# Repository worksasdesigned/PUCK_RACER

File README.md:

# Puck Racer 🏃‍♂️💨
**The DIY agility System**

## 📖 The Story: Why this exists
Let's be real for a second: I built this because I was simply too stingy to drop **300-400€** on a commercial reaction light system that consists of only 4 pucks, needs a paid subscription and provides 200 extremely similar games... which can be summerized in 5 different game modes.  
**Puck Racer has now 26 games**. Highly adjustable. Multi-Player, Multi-Group support.  
All options combined easily provide 200+ "games" ;-)  

I also noticed that the PE equipment at my kids' elementary school hasn't really changed in 40 years. It was time for an upgrade.

**Puck Racer** is the answer. It’s perfect for professional training support in sports clubs, spicing up PE lessons in schools, or just being the absolute highlight of the next kids' birthday party.  
I would descibe it as a **blaze**ing**POD** - DIY solution - just on steroids :-)  

**The Trade-off:**
Yes, building 4-10 Pucks and a Coordinator is a bit of a grind. It takes time and patience.

**The Reward:**
You get a fully customizable system where the hardware cost per Puck can be pushed **under 20€**. You do the math. 😉  
Nice side effect: Teach your kids how to solder. Its easy to medium difficulty. My 9 year old twins built 5 pucks by them selfe with very little help.  

---

## 🛠 Hardware
*detailed howto and hardware list will be provided once its worth it*  
ESP32-C3 for pucks   (use the one with external antenna or built a small antenna!)
ESP32-S3 for Coordinator  
WS2812B 35LED ring  
something for 18650 Battery placement + stepup to 5V  
Arcade Button (bigger is better) 60mm  
3D printer for pucks  
Soldering Stuff  
**P A T I E N C E** - printing 10 pucks, soldering 10 times the same stuff and initial flashing needs a good amount of patience.

---

## 💻 Software & Installation

This system relies on a **Coordinator** (ESP32-S3) that acts as the brain and the WiFi Access Point, and multiple **Pucks** (ESP32-C3) that communicate via ESP-NOW.

### 📦 Prerequisites

To compile and flash this project, you need the **Arduino IDE**. Of cause VS Code will also work. 

1.  **ESP32 Board Manager:**
    * Go to *Tools > Board > Boards Manager*.
    * Install **esp32 by Espressif Systems**.
    * **Recommended Version:** `3.0.0` or higher (we need proper S3/C3 support).

2.  **Required Libraries:**
    Install these via the Arduino Library Manager:
    * `FastLED` (for the WS2812B LEDs)
    * `ESPAsyncWebServer from ESPhome project` (for the Coordinator Dashboard)
    * `AsyncTCP from ESPhome project` (dependency for the WebServer)

### 📂 Uploading the Web Interface (IMPORTANT!)

The Coordinator runs a modern Web App stored in the ESP32's internal file system (LittleFS). You **must** upload the files from the `data` folder, otherwise, you'll just see a blank screen.

1.  Download the **Arduino LittleFS Upload Tool**:
    * 👉 [GitHub Link: arduino-littlefs-upload](https://github.com/earlephilhower/arduino-littlefs-upload)
2.  Follow the installation instructions on the repo (copy to `tools` folder).
3.  In Arduino IDE, select the Coordinator board.
4.  Click **Tools > ESP32 LittleFS Data Upload**.

### 📡 Connectivity & OTA Updates

**The Network:**
The Coordinator opens a WiFi Access Point (Default SSID: `PuckRace_Trainer`). Connect your phone or laptop to this network and navigate to `http://192.168.42.1`. No app required, it runs in the browser.  It has no pwassword initially. Your choice to set it up if you deal with kids and their smartphones.

**Wireless Updates (OTA):**
You only need to hook the Pucks up to USB *once* for the initial flash. After that, you're free:
1.  Compile the new Puck firmware (Sketch -> Export Compiled Binary).
2.  Go to the Coordinator Web Interface Settings.
3.  Upload the `.bin` file.
4.  Hit **"Update All Pucks"**. The Coordinator will distribute the update wirelessly to all active Pucks. Magic. ✨

After the real first beta is released il will provide the bin files in case of updates. 

---

## 🎮 The Games

**26 games** across 4 categories. Highly adjustable, multi-player and multi-group support.

| Focus | Icon |
|---|---|
| Hand-eye coordination, fast stimulus processing | ⚡ Reaction |
| Rapid direction changes, sprints, footwork | 🏃‍♂️ Agility |
| Cardiovascular load and pacing | 🫀 Endurance |
| Memory, timing, stress resistance | 🧠 Cognition |
| Teambuilding and motivation | 🤪 Fun |
| Practical tools for coaches and teachers | 🛠️ Utility |

---

### ⚡🏃‍♂️ Agility & Reaction

| Game | Players | Pucks | Focus | Highlights |
|------|---------|-------|-------|------------|
| 🎯 **Hunt! (Color Hunt)** | 1–10 | 3–20 | ⚡ 🏃‍♂️ 🧠 | Dynamic queues, adjustable timeout, 1-sec warning |
| ⚡ **React 2-Player** | 2–10 (pairs) | 3–10/group | ⚡ 🧠 | Configurable colors, fake stimuli for confusion |
| 🎯 **Target Touch** | 1–5 groups | 2–10/group | ⚡ 🛠️ | Sequence or random mode, rest time control |
| 🏃‍♂️ **Agility T-Test** | 1–2 groups | 4/group | 🏃‍♂️ | Standard T-test layout, mandatory touch mode |
| 🐱 **Cat Reflex** | 1–11 | 1/player + 1 center | ⚡ | Highlander mode, Color Chaos (false-start training) |
| ⚡🎯 **Catch the light Pro** | 1 | 3–20 | ⚡ 🧠 | Adaptive speed, fake colors, per-puck reaction analysis |

---

### 🫀 Endurance & Pacing

| Game | Players | Pucks | Focus | Highlights |
|------|---------|-------|-------|------------|
| ⏱️ **The Pacemaker** | Groups | 4–20 | 🫀 🧠 | Exact pace (min/km), circle or shuttle, live distance |
| 🏃‍♂️ **Luc Léger (Beep Test)** | 1–10 | 2/player | 🫀 | Official VO₂max tables, false start detection |
| 🏃‍♂️ **Shuttle Run** | 1–5 | 2/player | 🏃‍♂️ 🫀 | Winner detection, false start detection |
| 🧟 **Zombie Escape** | 1–10 groups | 2/group | 🫀 🧠 🤪 | Auto time reduction, sudden death mode |
| 🏎️ **Pit Stop** | 1–10 groups | 1-2/group | 🫀 | Making a break. Defined PitStops. Pitlane mode. |

---

### 🧠🤪 Cognition & Fun

| Game | Players | Pucks | Focus | Highlights |
|------|---------|-------|-------|------------|
| 🔴 **Simon Says** | 1–3 groups | 2–10/group | 🧠 | Adjustable speed, color-blind palette |
| 🏃‍♂️ **Simon Runs** | 1–3 groups | 1 display + inputs | 🧠 🏃‍♂️ | Central display mode, disqualification management |
| 💣 **Bomb Squad** | 1–10 | 1/player | 🧠 🤪 | Adjustable tolerance, group sync mode, explosion feedback |
| 🚦 **Red Light, Green Light** | 1–10 groups | 1–20 | 🤪 ⚡ | Grace period, coach override |
| 🎩 **The Sorting Hat** | 2–100 | 1–3 | 🛠️ 🤪 | Balanced assignment, live rebalance |
| 🧠 **Memory Sprint** | 1+ | 4–20 (pairs) | 🧠 🏃‍♂️ | Blind search mode, auto-restart, live error tracking |
| ⚔️ **Domination (Turf War)** | 2 teams/arena | 2+/arena | 🏃‍♂️ 🫀 | 1-click vs 2-click capture, dual-arena support |
| ❌⭕ **Tactical TicTacToe** | 1–3 groups | 4 / 6 / 7 / 10 | 🧠 | Hard-Mode, grid auto-adapts to puck count |
| 🪑 **Musical Chairs** | 2–13 | Player count −1 | 🤪 🏃‍♂️ | Custom MP3 upload, dynamic round elimination |

---

### 🛠️ Measurement Tools & Utilities

| Game | Players | Focus | Highlights |
|------|---------|-------|------------|
| ⏱️ **Stopwatch** | 1–10 | 🛠️ | Split/lap times, central or individual start, Hold-to-Start |
| ⏳ **Simple Timer** | 1–10 | 🛠️ | Visual countdown fill, live +/− time adjustment per player |
| 🔢 **Simple Counter** | 1–10 | 🛠️ | Tap-to-count, time limit, debounce filter |
| ⬇️ **Simple Countdown** | 1–10 | 🛠️ | Count down from N, stop-on-winner option |
| 🥵 **TABATA Controller** | Unlimited | 🛠️ 🫀 | Synced progress bars, work/rest phases, configurable sound |
| ▶️ **Display Mode** | — | 🛠️ | Manual/sync/random light control for events |

---

### 👥 Player & Training Manager

| Tool | Description |
|------|-------------|
| 👥 **Player Manager** | Manage teams and class lists. Upload/backup CSV. Create named groups for quick name assignment. |
| 📋 **Training Manager** | Define training sequences with up to 3 games and pre-set all parameters. Jump between games without touching the setup screens. |

---

## Technical Updates:  

**V2.88.2**  
    - iOS meta Tags added  
    - App Icon added  
    - Check that only 1 device is connected via WiFi  

**V2.89.7**   
    - Simple Statistics added for players maintained in Playermanager  
    - CatReflexes (avarage reaction time)  
    - BombSquad (avarage reaction time)  
    - Shuttle run (time) assuming trainer always uses same distance, else its just a tracking of usage  
    - Countdown (time and clicks) tracking of usage - Fix of copy&paste error in game_simplecounter_setup.html      
**V2.89.13**  
    - statistics for all relevant games finished  
        - Whac-A-Mole  
        - Pacemaker  
        - React2Player  
        - T-Test  
        - Beep Test  
        - Catch the light (incl. System record)  
    - Player manager with extended Export and Import incl. highscores and statistics   
    - Minor bugfixes in some games (Player-List added, minor layout changes)  
        - fix for Whac-A-Mole color picker  
**V2.89.15**   
    - Tutorial adjusted  

**V2.90.12**   
    - RSSI fixed  
    - 12 games small fixes (puck colo) fixed  
    - snall enhancements in various games after Beta Test 1  

**V2.91.1**   
    - new game: Pit Stop  
    - Red Light Green Light small adjustments and fixes  

**V2.92.3**   
    - rename a game to catch the light  
    - Cat Reflex Highlander Mode adjusted  

**V2.93.0**   
    - Bidirectional heartbeat puck firmware 81  

**V2.94.2**   
    - UI 2.0 new design    

**V2.96.1**   
    - Battery Management and auto Power Saving Mode   
    - Toast Message "low Battery level", "shutdown Puck due to critical battery level"   
    - Puck shutdown (deepsleep) at low Battery level (safety)   
    - Puck blocks reboot under 3,6V Battery level (safety)  
    - Max LED Power Consumption reduced to 1.2A (should only effect white @35LEDs) (safety)   
    - Hardware Watchdog implemented (Puck restarts after 3s off non-reactivity)   

**V2.97.1**   
    - Anti-cache links added (Core version behind urls)   
    - _setup.html remembers settings, when navigation back from _run to _names  to _setup.html    

**V2.98.0**   
    - Gerber and PCB files addes   
    - temperature control, warning and local alarm added   

**V2.99.1**   
    - Test version keygen working in react2p
    - Test version of JSON GAME   

**V3.0.1**   
    - change to OpenSource, Removed c Blocker of Licence key. HTML blocker stays for registration use  
    - Stabilization fix. passed 3h permanent test!   
    - many small fixes.  

--- 

## 🤝 Contributing
Found a bug? Have a game idea? Feel free to open an issue or submit a pull request. Let's make school sports digital (and affordable)!  
**Licence:** Use it, change it, DO NOT SELL it.  see License.txt

*Project by WorksAsDesigned*

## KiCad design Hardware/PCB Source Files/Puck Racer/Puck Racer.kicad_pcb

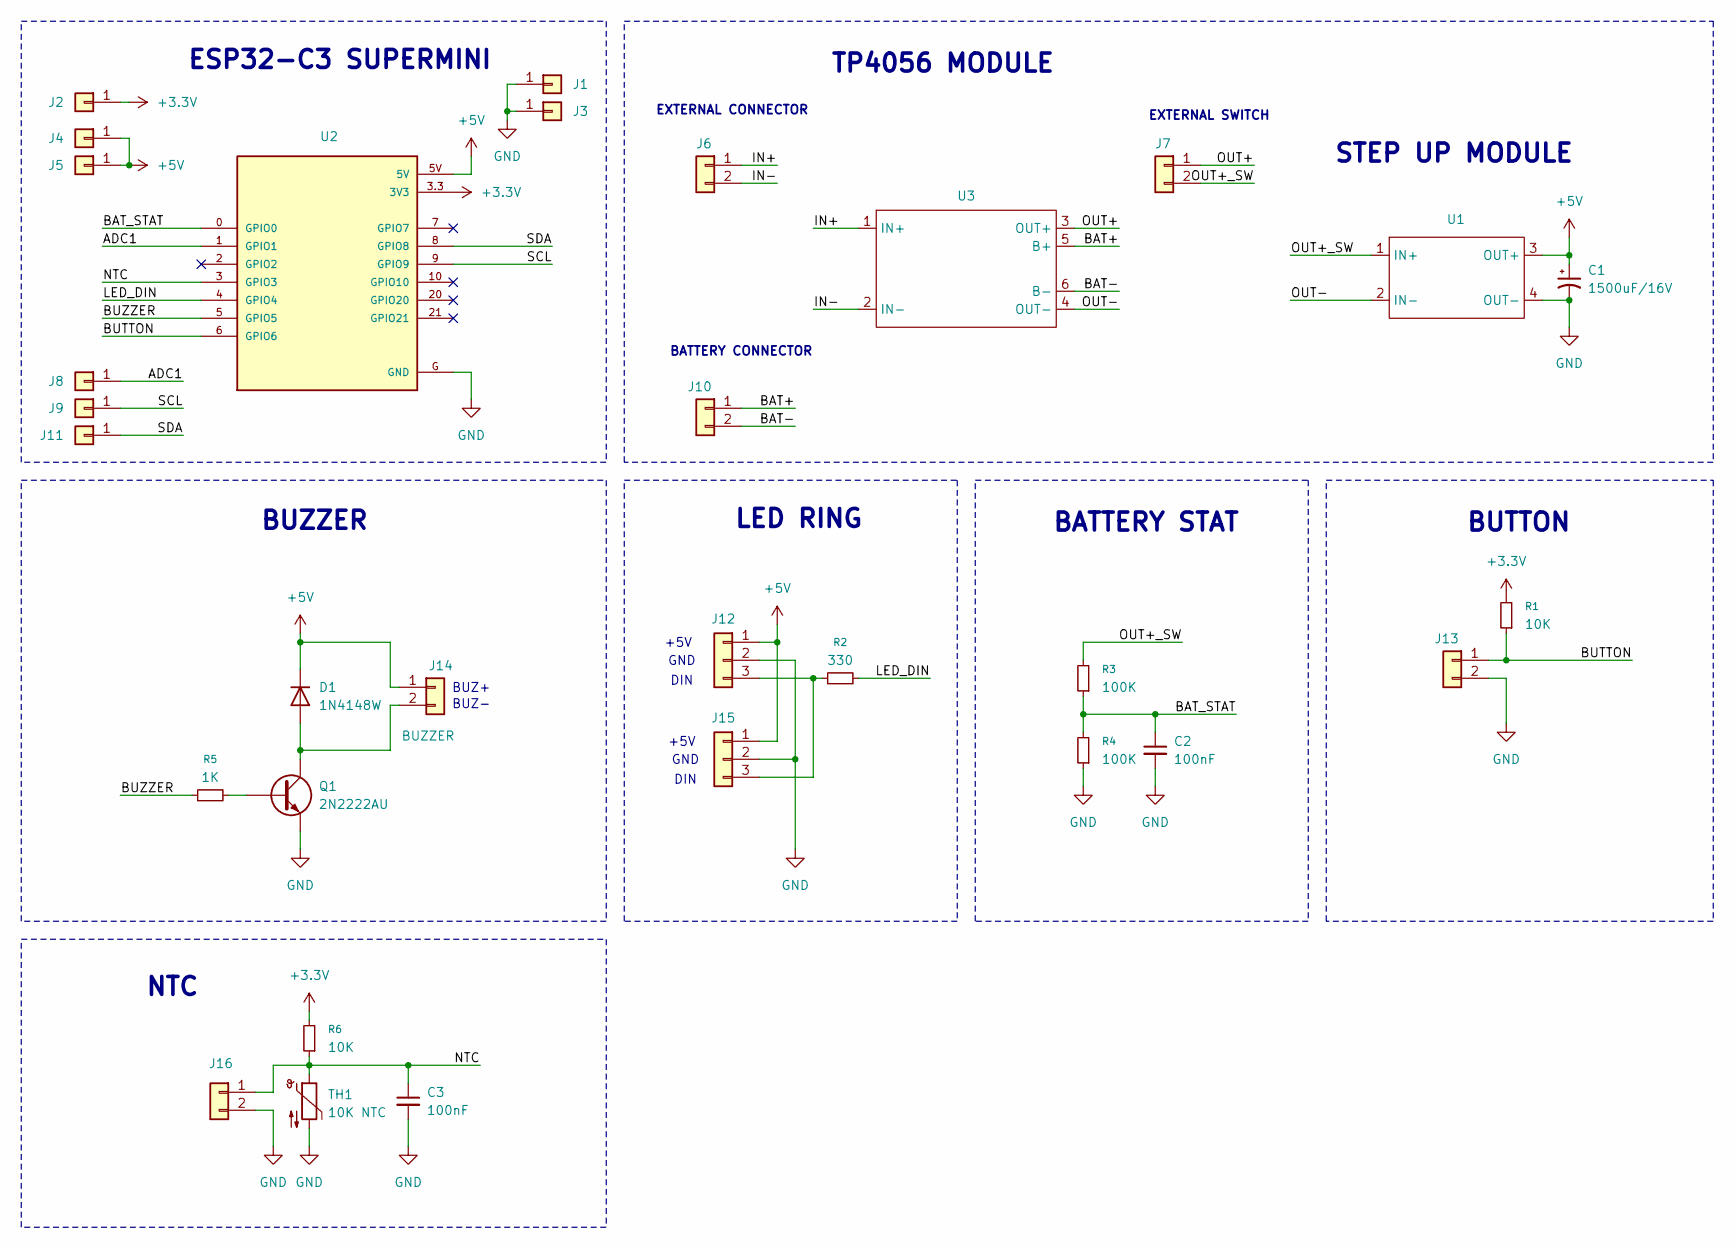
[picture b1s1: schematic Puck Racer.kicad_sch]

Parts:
C1: 1500uF/16V; CP_Radial_D10.0mm_P5.00mm
C2, C3: 100nF; C_0805_2012Metric; JLCPCB Part # C28233
D1: 1N4148W; D_SOD-123; JLCPCB Part # C2099
J1, J2, J3, J4, J5, J8, J9, J11: Conn_01x01; PinHeader_1x01_P2.54mm_Vertical
J6, J7, J10: B2B-XH-A(LF)(SN); JST_XH_B2B-XH-A_1x02_P2.50mm_Vertical; JLCPCB Part # C158012
J12: B3B-XH-A(LF)(SN); JST_XH_B3B-XH-A_1x03_P2.50mm_Vertical; JLCPCB Part # C144394
J13, J16: BUTTON1; PinHeader_1x02_P2.54mm_Vertical
J14: BUZZER; PinHeader_1x02_P2.54mm_Vertical
J15: LED; PinHeader_1x03_P2.54mm_Vertical
Q1: 2N2222AU; SOT-89-3; JLCPCB Part # C21714170
R1, R6: 10K; R_0805_2012Metric; JLCPCB Part # C17414
R2: 330; R_0805_2012Metric; JLCPCB Part # C17630
R3, R4: 100K; R_0805_2012Metric; JLCPCB Part # C25611
R5: 1K; R_0805_2012Metric; JLCPCB Part # C17513
TH1: 10K NTC; R_0805_2012Metric; JLCPCB Part # C95968
U1: Step Up Power Module
U2: ESP32-C3_SUPERMINI_TH; MODULE_ESP32-C3_SUPERMINI_TH
U3: TP4056 Module

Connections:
+3.3V: J2.1, R1.2, R6.2, U2.3.3 (3V3)
+5V: C1.1, D1.1 (K), J4.1, J5.1, J12.1, J14.1, J15.1, U1.3 (OUT+), U2.5V
/ADC1: J8.1, U2.1 (GPIO1)
/BAT+: J10.1, U3.5 (B+)
/BAT-: J10.2, U3.6 (B-)
/BAT_STAT: C2.1, R3.1, R4.2, U2.0 (GPIO0)
/BUTTON: J13.1, R1.1, U2.6 (GPIO6)
/BUZZER: R5.1, U2.5 (GPIO5)
/IN+: J6.1, U3.1 (IN+)
/IN-: J6.2, U3.2 (IN-)
/LED_DIN: R2.2, U2.4 (GPIO4)
/NTC: C3.1, J16.1, R6.1, TH1.1, U2.3 (GPIO3)
/OUT+: J7.1, U3.3 (OUT+)
/OUT+_SW: J7.2, R3.2, U1.1 (IN+)
/OUT-: U1.2 (IN-), U3.4 (OUT-)
/SCL: J9.1, U2.9 (GPIO9)
/SDA: J11.1, U2.8 (GPIO8)
GND: C1.2, C2.2, C3.2, J1.1, J3.1, J12.2, J13.2, J15.2, J16.2, Q1.3 (E), R4.1, TH1.2, U1.4 (OUT-), U2.G (GND)
unnamed: D1.2 (A), J14.2, Q1.2 (C)
unnamed: J12.3, J15.3, R2.1
unnamed: Q1.1 (B), R5.2

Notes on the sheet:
GND
BUTTON
STEP UP MODULE
BUZZER
DIN
NTC
LED RING
+5V
BUZ+
EXTERNAL CONNECTOR
EXTERNAL SWITCH
BATTERY STAT
BUZ-
TP4056 MODULE
BATTERY CONNECTOR
ESP32-C3 SUPERMINI

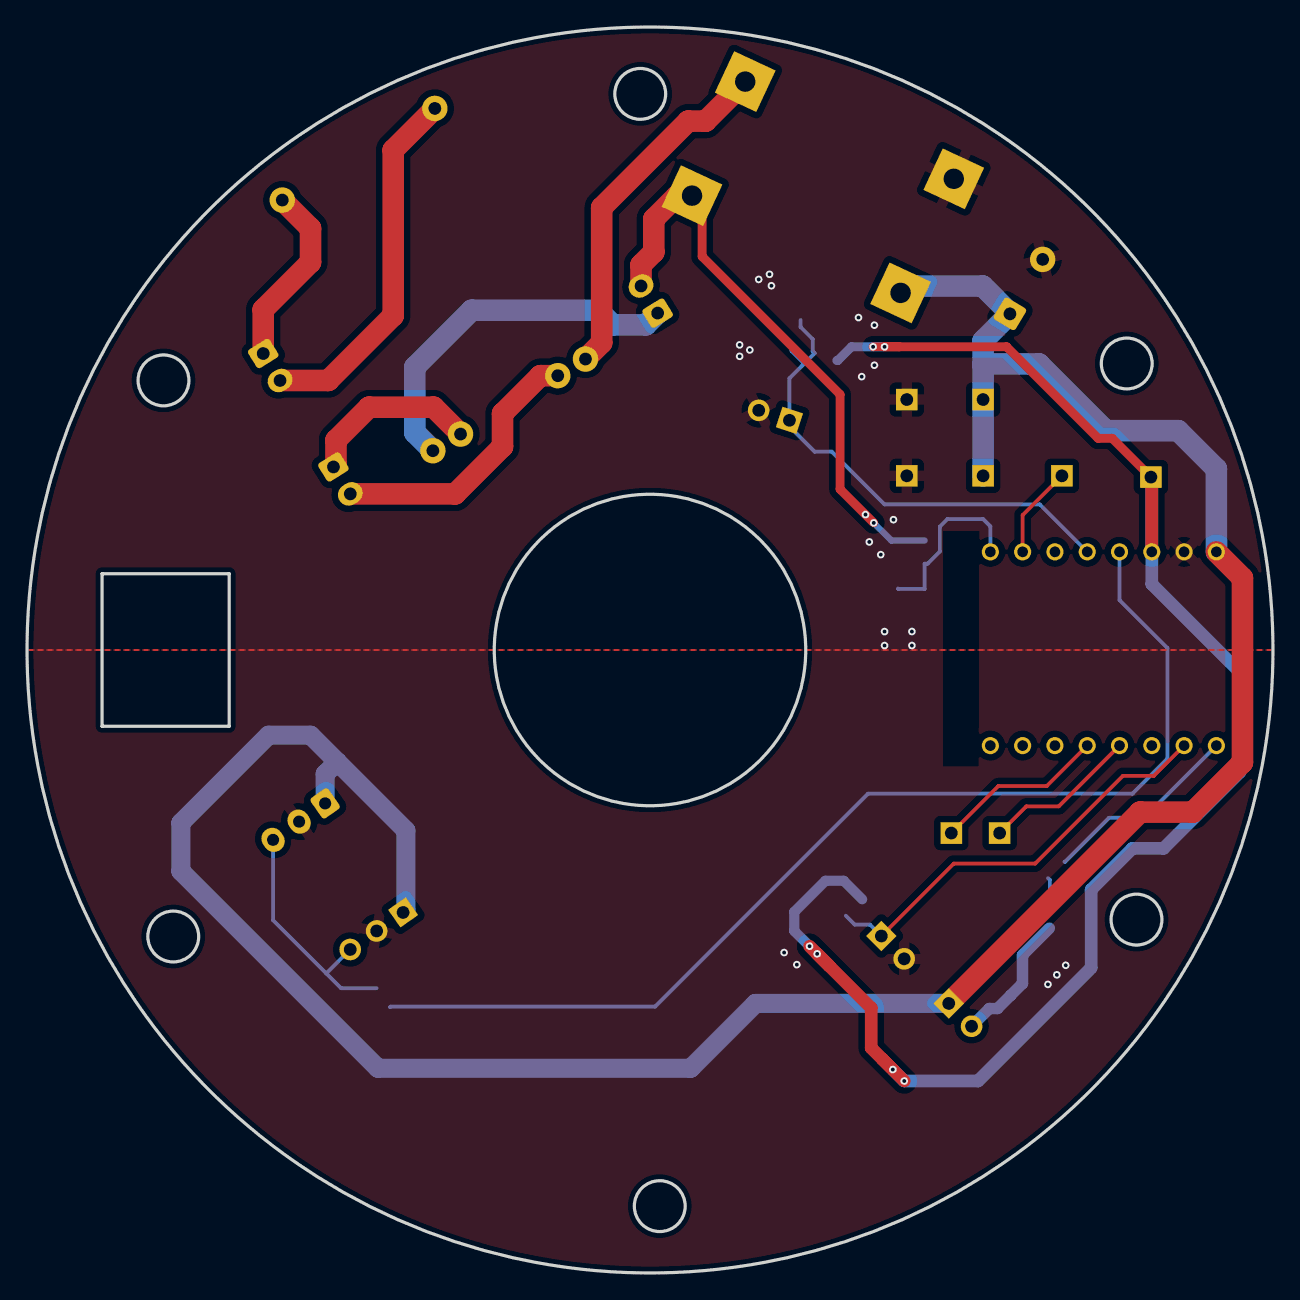
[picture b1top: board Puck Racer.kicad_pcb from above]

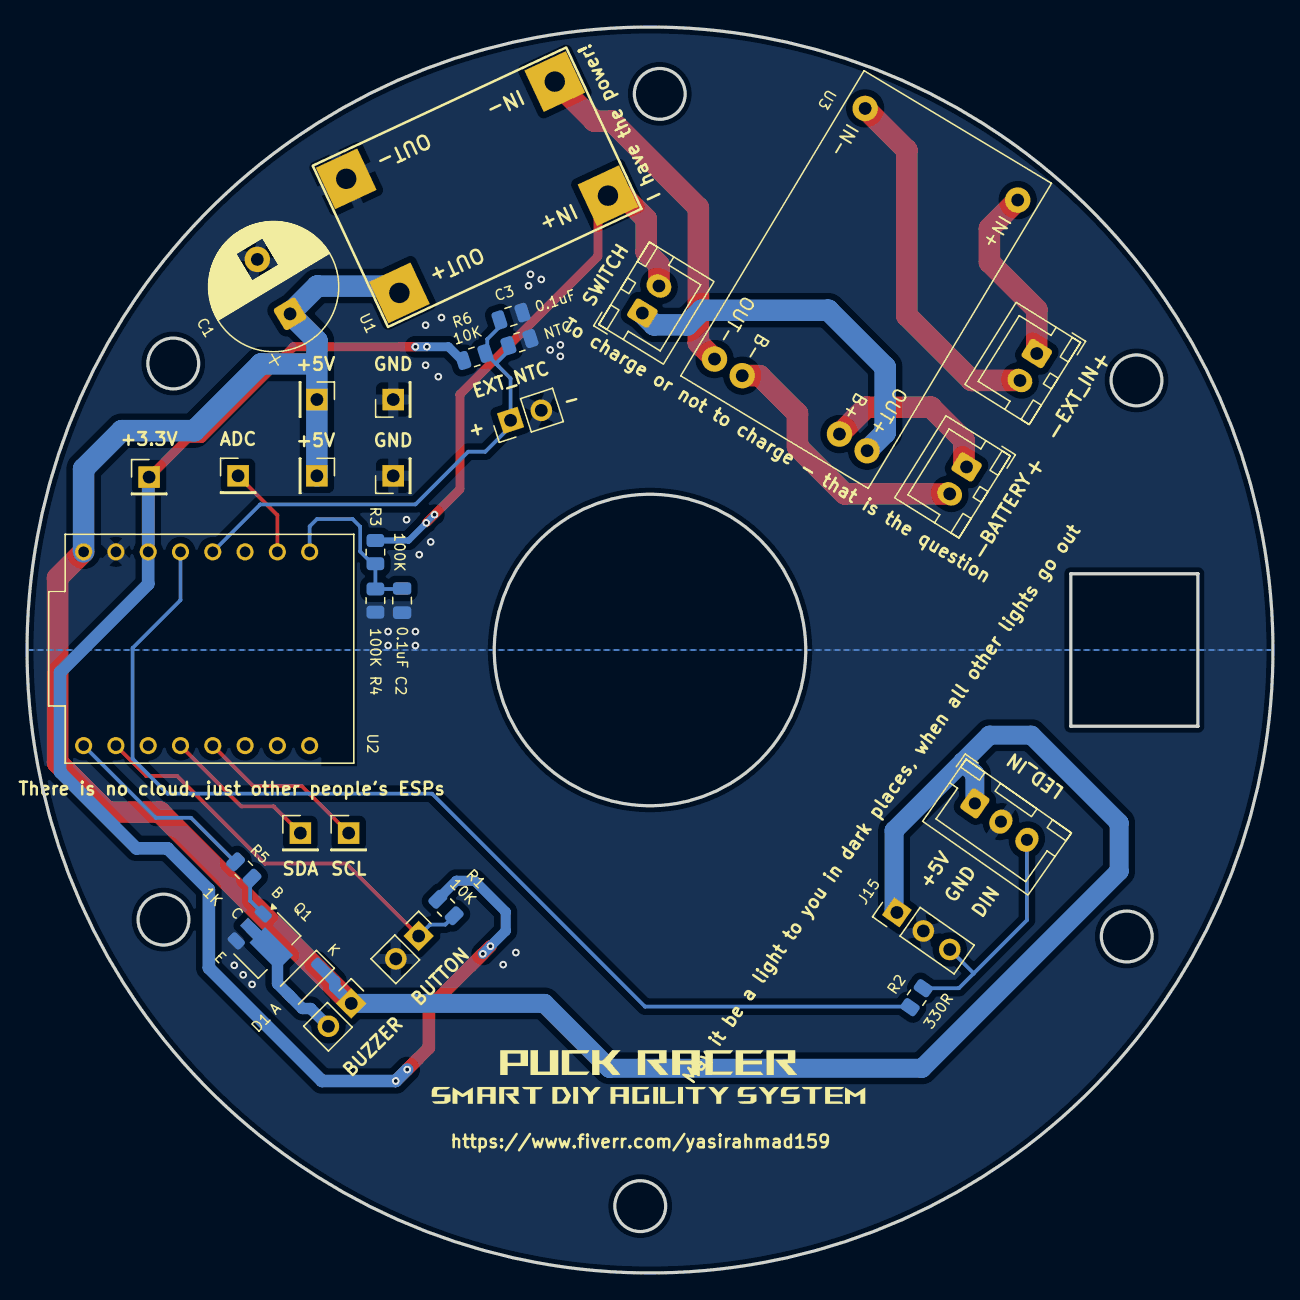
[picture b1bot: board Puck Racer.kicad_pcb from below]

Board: 2 copper layers, 98.0 x 98.0 mm, 31 parts (31 on the bottom side), 21 nets.

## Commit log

2026-03-10 readme added
2026-03-10 Only 1 device is allowed to be connected via webinterface
2026-03-10 V2.88.2 App Icon added, iOS meta Tags added to all HTML pages
2026-03-10 Statistik SimonSays und shuttle run, bugfix simon says_run
2026-03-12 Countdown_setup fix, Statistik in catreflexes, Bomb und Countdown
2026-03-12 V2.89.11 All relevant games added to statistics. PlayerManager updated
2026-03-13 V2.89.12 Fix Whac-A-Mole
2026-03-13 V2.89.13 Whac-A-Mol Fix
2026-03-13 V2.89.15 Added missing translations
2026-03-13 V2.89.14 lang.js restructured, tutorial improved
2026-03-16 V2.90.1 RSSI, Shuttlerun fix, Board Version 3.x/2.x mix
2026-03-16 V2.90.2 Color fix Simple Counter groups/pucks
2026-03-16 V2.90.3 fixed missing translation simple_counter
2026-03-16 V2.90.4 player color adjusted, puck color adjusted, game end player color fixed
2026-03-16 V2.90.5 small UX enhacement Stoppwatch GUI
2026-03-16 V2.90.6 Hide Central Display puck if only 1 group is selected, warning message added in _setup.html
2026-03-16 V2.90.7 setup and names puck color fix
2026-03-16 V2.90.8 sorting hat last group assignment not shown bug fixed
2026-03-16 V2.90.9 No puck effect in _setup.html
2026-03-16 V2.90.10 react2P individual group timer
2026-03-16 V2.90.10 timer fix
2026-03-17 V2.90.11 Pacemaker variable pace, 4 puck min check
2026-03-18 V2.90.12 only1device fix, small fix in simple timer
2026-03-20 V2.91.2 NEW Pitstop, redgreen bugfix
2026-03-21 V2.92.1 bugfix Hunt, new Deathmatch mode in Domination
2026-03-21 V2.92.3 Rename a game to Catch the light, fix CatReflex Highlander mode
2026-03-21 V2.92.4 missing translation
2026-03-21 V2.93.0 bidirectional heartbeat, no powersaving , network stability
2026-03-21 V2.93.0
2026-03-21 V2.93.0 bugfixes, pitstop, network stability
2026-03-21 V2.93.0 bugfixes and new game
2026-03-22 V2.94.2 images, UI V2.0
2026-03-23 V2.94.3 tutorial fix, statistic example / translation
2026-03-23 V2.95.0 UI2.0 update, pictures
2026-03-23 V82 HardwareWatchdog, max LED power consumption 1.2A@5V
2026-03-23 V2.95.1 / V82 small bugfixes HWD & pitstop
2026-03-23 V2.96.1 / V83 improved battery warning, RSSI sniffer checks MAC of Coordinator
2026-03-24 V2.96.1 Battery Management
2026-03-24 V2.97.0 all links anti cache with firmewareversion added
2026-03-24 V2.97.1 remember _setup parameters
2026-03-24 V2.97.1
2026-03-24 V2.97.2 new toast messages, new parameter page in settings.html
2026-03-24 update 3 to 4 MB max filesize
2026-03-24 V2.97.3 General mute button added
2026-03-24 V2.97.4 max brightness setting
2026-03-25 V2.97.5 show puckoverview in all html
2026-03-25 V2.97.3 reorganized setting.html as coverflow
2026-03-25 V2.97.6 new settings page
2026-03-25 V2.97.7 total play time, settings translated, timer default britness 33%
2026-03-25 V2.97.7 Variable battery warning, timer brightness adjusted to 33%
2026-03-26 V2.97.8 small adjustments + website
2026-03-26 V2.97.8 css adjustment
2026-03-26 V0.2 Website
2026-03-26 V0.3 webseite
2026-03-26 V0.3.1 webseite
2026-03-28 V0.4 webseite
2026-03-28 V2.98.0 Thermal control of Puck inside, Warning, shutdown. Hardware files Added for PCB
2026-03-28 V2.98.0 UI update, temp control, website, new settings page, battery warning
2026-03-28 V2.98.0
2026-03-29 V2.99.0 test activation, ai summery
2026-03-29 V2.99.1 webbased Shareware version check + JSON Game test
2026-04-16 V2.99.5 Fix Font windows, UI adjustments, small bugfixes
2026-04-16 V2.99.6 RC1 webflasher
2026-05-19 V3.0.0 stable Open source
2026-05-19 V3.0.0
2026-05-19 V3.0.1 small adjustments and bugfixes
